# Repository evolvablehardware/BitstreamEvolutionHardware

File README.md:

# BitstreamEvolutionHardware
Documentation and resources for Hardware components for the Bitstream Evolution technology platform.

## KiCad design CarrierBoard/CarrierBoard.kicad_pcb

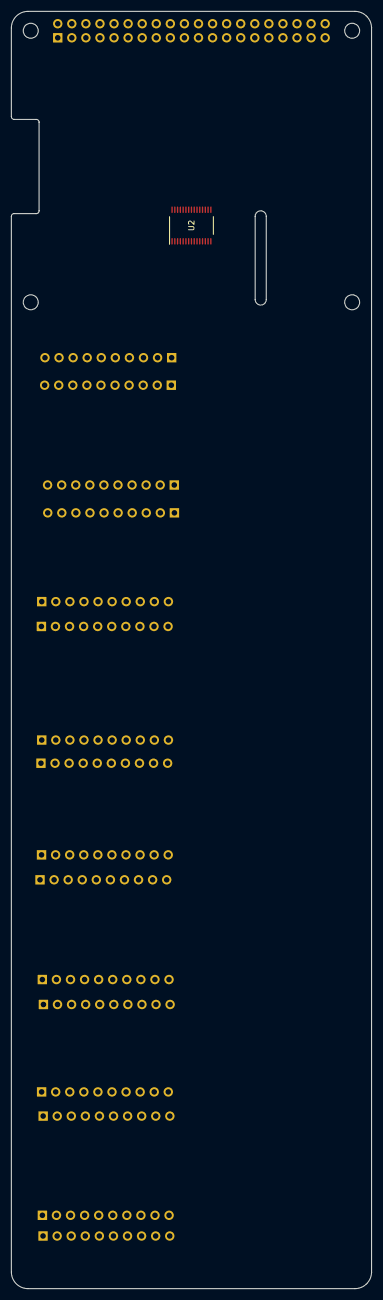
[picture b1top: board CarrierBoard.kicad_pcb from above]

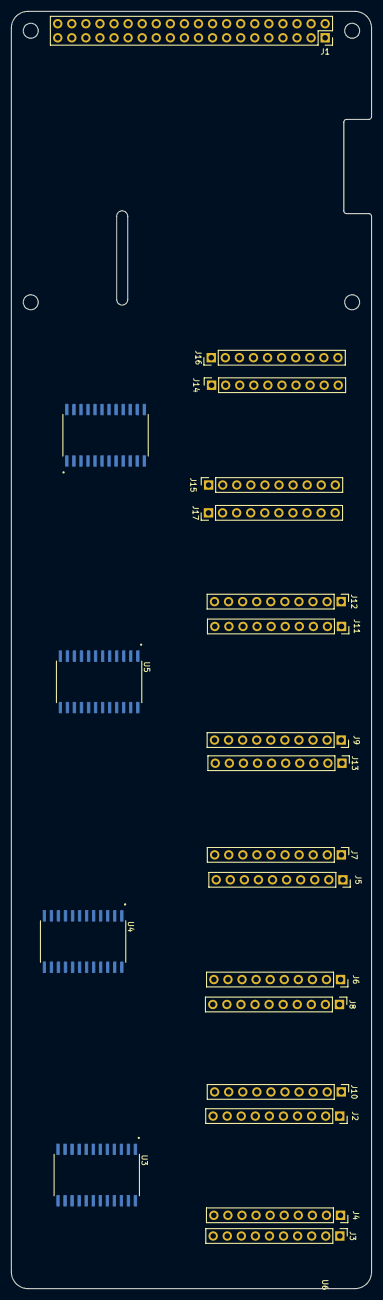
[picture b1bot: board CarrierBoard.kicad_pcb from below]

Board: 2 copper layers, 65.0 x 230.5 mm, 26 parts (21 on the bottom side), 68 nets, no tracks yet.

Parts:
J1: GPIO; PinSocket_2x20_P2.54mm_Vertical
J2, J4, J5, J6, J9, J11, J14, J15: Conn_01x10; PinSocket_1x10_P2.54mm_Vertical
J3, J7, J8, J10, J12, J13, J16, J17: Conn_01x10_Pin; PinHeader_1x10_P2.54mm_Vertical
MH1, MH2, MH3, MH4: MountingHole_2.7mm_M2.5
U2: ADS7950; DBT0030A_L
U3, U4, U5, U6: CD74HC4067M96; SOIC127P1030X265-24N

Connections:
+3V3: J1.1, J1.17
+5V: J1.2, J1.4, U3.24 (VCC), U4.24 (VCC), U5.24 (VCC), U6.24 (VCC)
/FPGA_0_0: J2.3, J10.3, U3.9 (I0)
/FPGA_0_1: J2.4, J10.4, U3.8 (I1)
/FPGA_0_2: J2.5, J10.5, U3.7 (I2)
/FPGA_0_3: J2.6, J10.6, U3.6 (I3)
/FPGA_0_4: J2.7, J10.7, U3.5 (I4)
/FPGA_0_5: J2.8, J10.8, U3.4 (I5)
/FPGA_0_6: J2.9, J10.9, U3.3 (I6)
/FPGA_0_7: J2.10, J10.10, U3.2 (I7)
/FPGA_0_8: J3.3, J4.3, U3.23 (I8)
/FPGA_0_9: J3.4, J4.4, U3.22 (I9)
/FPGA_0_10: J3.5, J4.5, U3.21 (I10)
/FPGA_0_11: J3.6, J4.6, U3.20 (I11)
/FPGA_0_12: J3.7, J4.7, U3.19 (I12)
/FPGA_0_13: J3.8, J4.8, U3.18 (I13)
/FPGA_0_14: J3.9, J4.9, U3.17 (I14)
/FPGA_0_15: J3.10, J4.10, U3.16 (I15)
/FPGA_1_0: J5.3, J7.3, U4.9 (I0)
/FPGA_1_1: J5.4, J7.4, U4.8 (I1)
/FPGA_1_2: J5.5, J7.5, U4.7 (I2)
/FPGA_1_3: J5.6, J7.6, U4.6 (I3)
/FPGA_1_4: J5.7, J7.7, U4.5 (I4)
/FPGA_1_5: J5.8, J7.8, U4.4 (I5)
/FPGA_1_6: J5.9, J7.9, U4.3 (I6)
/FPGA_1_7: J5.10, J7.10, U4.2 (I7)
/FPGA_1_8: J6.3, J8.3, U4.23 (I8)
/FPGA_1_9: J6.4, J8.4, U4.22 (I9)
/FPGA_1_10: J6.5, J8.5, U4.21 (I10)
/FPGA_1_11: J6.6, J8.6, U4.20 (I11)
/FPGA_1_12: J6.7, J8.7, U4.19 (I12)
/FPGA_1_13: J6.8, J8.8, U4.18 (I13)
/FPGA_1_14: J6.9, J8.9, U4.17 (I14)
/FPGA_1_15: J6.10, J8.10, U4.16 (I15)
/FPGA_2_0: J9.3, J12.3, U5.9 (I0)
/FPGA_2_1: J9.4, J12.4, U5.8 (I1)
/FPGA_2_2: J9.5, J12.5, U5.7 (I2)
/FPGA_2_3: J9.6, J12.6, U5.6 (I3)
/FPGA_2_4: J9.7, J12.7, U5.5 (I4)
/FPGA_2_5: J9.8, J12.8, U5.4 (I5)
/FPGA_2_6: J9.9, J12.9, U5.3 (I6)
/FPGA_2_7: J9.10, J12.10, U5.2 (I7)
/FPGA_2_8: J11.3, J13.3, U5.23 (I8)
/FPGA_2_9: J11.4, J13.4, U5.22 (I9)
/FPGA_2_10: J11.5, J13.5, U5.21 (I10)
/FPGA_2_11: J11.6, J13.6, U5.20 (I11)
/FPGA_2_12: J11.7, J13.7, U5.19 (I12)
/FPGA_2_13: J11.8, J13.8, U5.18 (I13)
/FPGA_2_14: J11.9, J13.9, U5.17 (I14)
/FPGA_2_15: J11.10, J13.10, U5.16 (I15)
/FPGA_3_0: J14.3, J16.3, U6.9 (I0)
/FPGA_3_1: J14.4, J16.4, U6.8 (I1)
/FPGA_3_2: J14.5, J16.5, U6.7 (I2)
/FPGA_3_3: J14.6, J16.6, U6.6 (I3)
/FPGA_3_4: J14.7, J16.7, U6.5 (I4)
/FPGA_3_5: J14.8, J16.8, U6.4 (I5)
/FPGA_3_6: J14.9, J16.9, U6.3 (I6)
/FPGA_3_7: J14.10, J16.10, U6.2 (I7)
/FPGA_3_8: J15.3, J17.3, U6.23 (I8)
/FPGA_3_9: J15.4, J17.4, U6.22 (I9)
/FPGA_3_10: J15.5, J17.5, U6.21 (I10)
/FPGA_3_11: J15.6, J17.6, U6.20 (I11)
/FPGA_3_12: J15.7, J17.7, U6.19 (I12)
/FPGA_3_13: J15.8, J17.8, U6.18 (I13)
/FPGA_3_14: J15.9, J17.9, U6.17 (I14)
/FPGA_3_15: J15.10, J17.10, U6.16 (I15)
GND: J1.6, J1.9, J1.14, J1.20, J1.25, J1.30, J1.34, J1.39, J2.2, J3.2, J4.2, J5.2, J6.2, J7.2, J8.2, J9.2, J10.2, J11.2, J12.2, J13.2, J14.2, J15.2, J16.2, J17.2, U3.12 (GND), U3.15 (~E), U4.12 (GND), U4.15 (~E), U5.12 (GND), U5.15 (~E), U6.12 (GND), U6.15 (~E)
unnamed: U2.6 (AGND), U2.10 (AGND), U2.22 (AGND)
